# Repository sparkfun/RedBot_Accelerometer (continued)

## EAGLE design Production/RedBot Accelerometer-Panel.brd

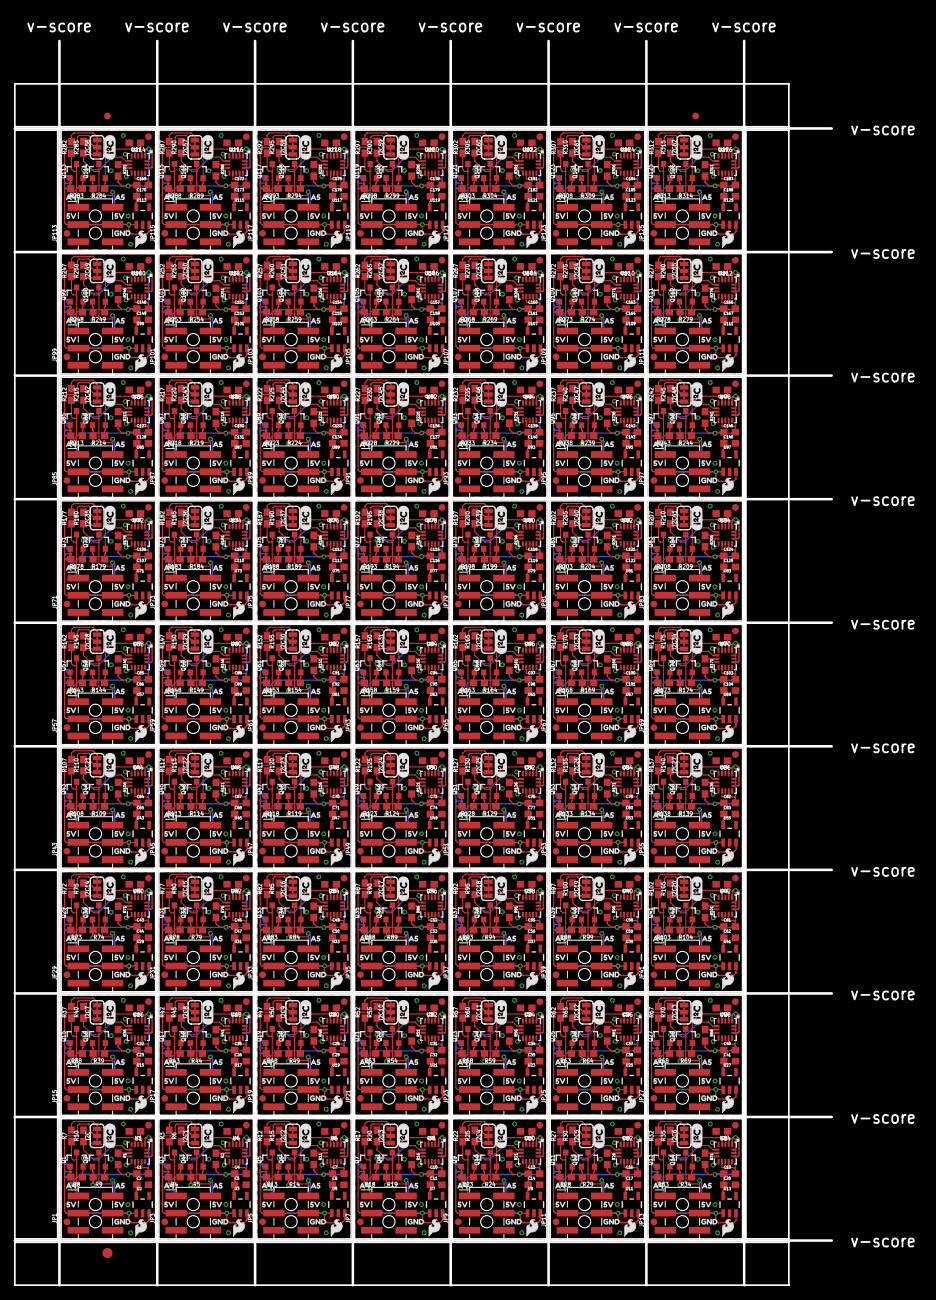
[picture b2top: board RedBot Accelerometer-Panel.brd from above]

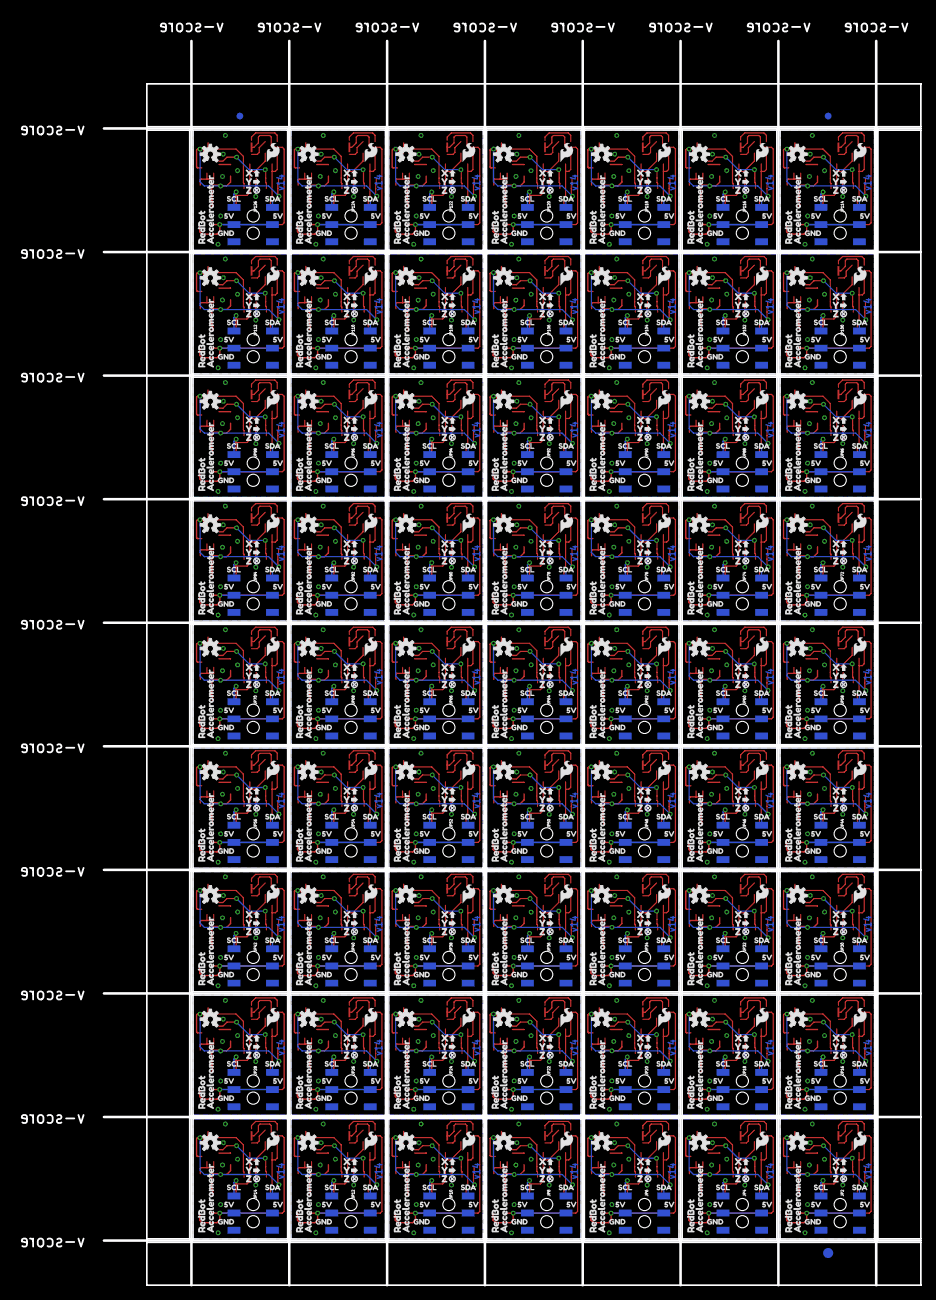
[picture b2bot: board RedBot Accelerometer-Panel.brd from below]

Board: 2 copper layers, 120.9 x 184.2 mm, 2400 parts (948 on the bottom side), 693 nets.

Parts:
C1, C3, C4, C6, C7, C9, C10, C12, C13, C15, C16, C18, C19, C21, C22, C24, C25, C27, C28, C30, C31, C33, C34, C36, C37, C39, C40, C42, C43, C45, C46, C48, C49, C51, C52, C54, C55, C57, C58, C60, C61, C63, C64, C66, C67, C69, C70, C72, C73, C75, C76, C78, C79, C81, C82, C84, C85, C87, C88, C90, C91, C93, C94, C96, C97, C99, C100, C102, C103, C105, C106, C108, C109, C111, C112, C114, C115, C117, C118, C120, C121, C123, C124, C126, C127, C129, C130, C132, C133, C135, C136, C138, C139, C141, C142, C144, C145, C147, C148, C150, C151, C153, C154, C156, C157, C159, C160, C162, C163, C165, C166, C168, C169, C171, C172, C174, C175, C177, C178, C180, C181, C183, C184, C186, C187, C189: 0.1uF; 0603
C2, C5, C8, C11, C14, C17, C20, C23, C26, C29, C32, C35, C38, C41, C44, C47, C50, C53, C56, C59, C62, C65, C68, C71, C74, C77, C80, C83, C86, C89, C92, C95, C98, C101, C104, C107, C110, C113, C116, C119, C122, C125, C128, C131, C134, C137, C140, C143, C146, C149, C152, C155, C158, C161, C164, C167, C170, C173, C176, C179, C182, C185, C188: 4.7uF; 0603
E$1, E$2, E$3, E$4: FIDUCIAL-1X2
E$5, E$6: FIDUCIAL-1.5X3
FID1, FID2, FID3, FID4, FID5, FID6, FID7, FID8, FID9, FID10, FID11, FID12, FID13, FID14, FID15, FID16, FID17, FID18, FID19, FID20, FID21, FID22, FID23, FID24, FID25, FID26, FID27, FID28, FID29, FID30, FID31, FID32, FID33, FID34, FID35, FID36, FID37, FID38, FID39, FID40, FID41, FID42, FID43, FID44, FID45, FID46, FID47, FID48, FID49, FID50, FID51, FID52, FID53, FID54, FID55, FID56, FID57, FID58, FID59, FID60, FID61, FID62, FID63, FID64, FID65, FID66, FID67, FID68, FID69, FID70, FID71, FID72, FID73, FID74, FID75, FID76, FID77, FID78, FID79, FID80, FID81, FID82, FID83, FID84, FID85, FID86, FID87, FID88, FID89, FID90, FID91, FID92, FID93, FID94, FID95, FID96, FID97, FID98, FID99, FID100, FID101, FID102, FID103, FID104, FID105, FID106, FID107, FID108, FID109, FID110, FID111, FID112, FID113, FID114, FID115, FID116, FID117, FID118, FID119, FID120, FID121, FID122, FID123, FID124, FID125, FID126: FIDUCIAL1X2; FIDUCIAL-1X2
I2C, I2C1, I2C2, I2C3, I2C4, I2C5, I2C6, I2C7, I2C8, I2C9, I2C10, I2C11, I2C12, I2C13, I2C14, I2C15, I2C16, I2C17, I2C18, I2C19, I2C20, I2C21, I2C22, I2C23, I2C24, I2C25, I2C26, I2C27, I2C28, I2C29, I2C30, I2C31, I2C32, I2C33, I2C34, I2C35, I2C36, I2C37, I2C38, I2C39, I2C40, I2C41, I2C42, I2C43, I2C44, I2C45, I2C46, I2C47, I2C48, I2C49, I2C50, I2C51, I2C52, I2C53, I2C54, I2C55, I2C56, I2C57, I2C58, I2C59, I2C60, I2C61, I2C62: JUMPER-SMT_3_2-NC_TRACE_SILK; SMT-JUMPER_3_2-NC_TRACE_SILK
JP1, JP3, JP5, JP7, JP9, JP11, JP13, JP15, JP17, JP19, JP21, JP23, JP25, JP27, JP29, JP31, JP33, JP35, JP37, JP39, JP41, JP43, JP45, JP47, JP49, JP51, JP53, JP55, JP57, JP59, JP61, JP63, JP65, JP67, JP69, JP71, JP73, JP75, JP77, JP79, JP81, JP83, JP85, JP87, JP89, JP91, JP93, JP95, JP97, JP99, JP101, JP103, JP105, JP107, JP109, JP111, JP113, JP115, JP117, JP119, JP121, JP123, JP125: 2X3_SMT_POSTS
JP2, JP4, JP6, JP8, JP10, JP12, JP14, JP16, JP18, JP20, JP22, JP24, JP26, JP28, JP30, JP32, JP34, JP36, JP38, JP40, JP42, JP44, JP46, JP48, JP50, JP52, JP54, JP56, JP58, JP60, JP62, JP64, JP66, JP68, JP70, JP72, JP74, JP76, JP78, JP80, JP82, JP84, JP86, JP88, JP90, JP92, JP94, JP96, JP98, JP100, JP102, JP104, JP106, JP108, JP110, JP112, JP114, JP116, JP118, JP120, JP122, JP124, JP126: 2X3_SMD
LOGO1, LOGO2, LOGO7, LOGO10, LOGO13, LOGO16, LOGO19, LOGO22, LOGO25, LOGO28, LOGO31, LOGO34, LOGO37, LOGO40, LOGO43, LOGO46, LOGO49, LOGO52, LOGO55, LOGO58, LOGO61, LOGO64, LOGO67, LOGO70, LOGO73, LOGO76, LOGO79, LOGO82, LOGO85, LOGO88, LOGO91, LOGO94, LOGO97, LOGO100, LOGO103, LOGO106, LOGO109, LOGO112, LOGO115, LOGO118, LOGO121, LOGO124, LOGO127, LOGO130, LOGO133, LOGO136, LOGO139, LOGO142, LOGO145, LOGO148, LOGO151, LOGO154, LOGO157, LOGO160, LOGO163, LOGO166, LOGO169, LOGO172, LOGO175, LOGO178, LOGO181, LOGO184, LOGO187: OSHW-LOGOS; OSHW-LOGO-S
LOGO3, LOGO5, LOGO8, LOGO11, LOGO14, LOGO17, LOGO20, LOGO23, LOGO26, LOGO29, LOGO32, LOGO35, LOGO38, LOGO41, LOGO44, LOGO47, LOGO50, LOGO53, LOGO56, LOGO59, LOGO62, LOGO65, LOGO68, LOGO71, LOGO74, LOGO77, LOGO80, LOGO83, LOGO86, LOGO89, LOGO92, LOGO95, LOGO98, LOGO101, LOGO104, LOGO107, LOGO110, LOGO113, LOGO116, LOGO119, LOGO122, LOGO125, LOGO128, LOGO131, LOGO134, LOGO137, LOGO140, LOGO143, LOGO146, LOGO149, LOGO152, LOGO155, LOGO158, LOGO161, LOGO164, LOGO167, LOGO170, LOGO173, LOGO176, LOGO179, LOGO182, LOGO185, LOGO188: LOGO-SFESK; SFE-LOGO-FLAME
LOGO4, LOGO6, LOGO9, LOGO12, LOGO15, LOGO18, LOGO21, LOGO24, LOGO27, LOGO30, LOGO33, LOGO36, LOGO39, LOGO42, LOGO45, LOGO48, LOGO51, LOGO54, LOGO57, LOGO60, LOGO63, LOGO66, LOGO69, LOGO72, LOGO75, LOGO78, LOGO81, LOGO84, LOGO87, LOGO90, LOGO93, LOGO96, LOGO99, LOGO102, LOGO105, LOGO108, LOGO111, LOGO114, LOGO117, LOGO120, LOGO123, LOGO126, LOGO129, LOGO132, LOGO135, LOGO138, LOGO141, LOGO144, LOGO147, LOGO150, LOGO153, LOGO156, LOGO159, LOGO162, LOGO165, LOGO168, LOGO171, LOGO174, LOGO177, LOGO180, LOGO183, LOGO186, LOGO189: SFE_LOGO_FLAME.1_INCH; SFE_LOGO_FLAME_.1
Q1, Q2, Q3, Q4, Q5, Q6, Q7, Q8, Q9, Q10, Q11, Q12, Q13, Q14, Q15, Q16, Q17, Q18, Q19, Q20, Q21, Q22, Q23, Q24, Q25, Q26, Q27, Q28, Q29, Q30, Q31, Q32, Q33, Q34, Q35, Q36, Q37, Q38, Q39, Q40, Q41, Q42, Q43, Q44, Q45, Q46, Q47, Q48, Q49, Q50, Q51, Q52, Q53, Q54, Q55, Q56, Q57, Q58, Q59, Q60, Q61, Q62, Q63, Q64, Q65, Q66, Q67, Q68, Q69, Q70, Q71, Q72, Q73, Q74, Q75, Q76, Q77, Q78, Q79, Q80, Q81, Q82, Q83, Q84, Q85, Q86, Q87, Q88, Q89, Q90, Q91, Q92, Q93, Q94, Q95, Q96, Q97, Q98, Q99, Q100, Q101, Q102, Q103, Q104, Q105, Q106, Q107, Q108, Q109, Q110, Q111, Q112, Q113, Q114, Q115, Q116, Q117, Q118, Q119, Q120, Q121, Q122, Q123, Q124, Q125, Q126: 220mA/50V/3.5Ω; SOT23-3
R1, R2, R3, R4, R5, R6, R7, R8, R9, R10, R11, R12, R13, R14, R15, R16, R17, R18, R19, R20, R21, R22, R23, R24, R25, R26, R27, R28, R29, R30, R31, R32, R33, R34, R35, R36, R37, R38, R39, R40, R41, R42, R43, R44, R45, R46, R47, R48, R49, R50, R51, R52, R53, R54, R55, R56, R57, R58, R59, R60, R61, R62, R63, R64, R65, R66, R67, R68, R69, R70, R71, R72, R73, R74, R75, R76, R77, R78, R79, R80, R81, R82, R83, R84, R85, R86, R87, R88, R89, R90, R91, R92, R93, R94, R95, R96, R97, R98, R99, R100, R101, R102, R103, R104, R105, R106, R107, R108, R109, R110, R111, R112, R113, R114, R115, R116, R117, R118, R119, R120, R121, R122, R123, R124, R125, R126, R127, R128, R129, R130, R131, R132, R133, R134, R135, R136, R137, R138, R139, R140, R141, R142, R143, R144, R145, R146, R147, R148, R149, R150, R151, R152, R153, R154, R155, R156, R157, R158, R159, R160, R161, R162, R163, R164, R165, R166, R167, R168, R169, R170, R171, R172, R173, R174, R175, R176, R177, R178, R179, R180, R181, R182, R183, R184, R185, R186, R187, R188, R189, R190, R191, R192, R193, R194, R195, R196, R197, R198, R199, R200, R201, R202, R203, R204, R205, R206, R207, R208, R209, R210, R211, R212, R213, R214, R215, R216, R217, R218, R219, R220, R221, R222, R223, R224, R225, R226, R227, R228, R229, R230, R231, R232, R233, R234, R235, R236, R237, R238, R239, R240, R241, R242, R243, R244, R245, R246, R247, R248, R249, R250, R251, R252, R253, R254, R255, R256, R257, R258, R259, R260, R261, R262, R263, R264, R265, R266, R267, R268, R269, R270, R271, R272, R273, R274, R275, R276, R277, R278, R279, R280, R281, R282, R283, R284, R285, R286, R287, R288, R289, R290, R291, R292, R293, R294, R295, R296, R297, R298, R299, R300, R301, R302, R303, R304, R305, R306, R307, R308, R309, R310, R311, R312, R313, R314, R315: 10k; 0603
U1, U4, U6, U8, U10, U12, U14, U16, U18, U20, U22, U24, U26, U28, U30, U32, U34, U36, U38, U40, U42, U44, U46, U48, U50, U52, U54, U56, U58, U60, U62, U64, U66, U68, U70, U72, U74, U76, U78, U80, U82, U84, U86, U88, U90, U92, U94, U96, U98, U100, U102, U104, U106, U108, U110, U112, U114, U116, U118, U120, U122, U124, U126: MMA8452Q; QFN-16
U2, U3, U5, U7, U9, U11, U13, U15, U17, U19, U21, U23, U25, U27, U29, U31, U33, U35, U37, U39, U41, U43, U45, U47, U49, U51, U53, U55, U57, U59, U61, U63, U65, U67, U69, U71, U73, U75, U77, U79, U81, U83, U85, U87, U89, U91, U93, U95, U97, U99, U101, U103, U105, U107, U109, U111, U113, U115, U117, U119, U121, U123, U125: MIC5205-3.3V; SOT23-5
U$1, U$18, U$37, U$55, U$73, U$91, U$109, U$127, U$145, U$163, U$181, U$199, U$217, U$235, U$253, U$271, U$289, U$307, U$325, U$343, U$361, U$379, U$397, U$415, U$433, U$451, U$469, U$487, U$505, U$523, U$541, U$559, U$577, U$595, U$613, U$631, U$649, U$667, U$685, U$703, U$721, U$739, U$757, U$775, U$793, U$811, U$829, U$847, U$865, U$883, U$901, U$919, U$937, U$955, U$973, U$991, U$1009, U$1027, U$1045, U$1063, U$1081, U$1099, U$1117: X0
U$2, U$20, U$38, U$56, U$74, U$92, U$110, U$128, U$146, U$164, U$182, U$200, U$218, U$236, U$254, U$272, U$290, U$308, U$326, U$344, U$362, U$380, U$398, U$416, U$434, U$452, U$470, U$488, U$506, U$524, U$542, U$560, U$578, U$596, U$614, U$632, U$650, U$668, U$686, U$704, U$722, U$740, U$758, U$776, U$794, U$812, U$830, U$848, U$866, U$884, U$902, U$920, U$938, U$956, U$974, U$992, U$1010, U$1028, U$1046, U$1064, U$1082, U$1100, U$1118: A42
U$3, U$21, U$39, U$57, U$75, U$93, U$111, U$129, U$147, U$165, U$183, U$201, U$219, U$237, U$255, U$273, U$291, U$309, U$327, U$345, U$363, U$381, U$399, U$417, U$435, U$453, U$471, U$489, U$507, U$525, U$543, U$561, U$579, U$597, U$615, U$633, U$651, U$669, U$687, U$705, U$723, U$741, U$759, U$777, U$795, U$813, U$831, U$849, U$867, U$885, U$903, U$921, U$939, U$957, U$975, U$993, U$1011, U$1029, U$1047, U$1065, U$1083, U$1101, U$1119: A53
U$4, U$5, U$8, U$11, U$22, U$23, U$26, U$29, U$40, U$41, U$44, U$47, U$58, U$59, U$62, U$65, U$76, U$77, U$80, U$83, U$94, U$95, U$98, U$101, U$112, U$113, U$116, U$119, U$130, U$131, U$134, U$137, U$148, U$149, U$152, U$155, U$166, U$167, U$170, U$173, U$184, U$185, U$188, U$191, U$202, U$203, U$206, U$209, U$220, U$221, U$224, U$227, U$238, U$239, U$242, U$245, U$256, U$257, U$260, U$263, U$274, U$275, U$278, U$281, U$292, U$293, U$296, U$299, U$310, U$311, U$314, U$317, U$328, U$329, U$332, U$335, U$346, U$347, U$350, U$353, U$364, U$365, U$368, U$371, U$382, U$383, U$386, U$389, U$400, U$401, U$404, U$407, U$418, U$419, U$422, U$425, U$436, U$437, U$440, U$443, U$454, U$455, U$458, U$461, U$472, U$473, U$476, U$479, U$490, U$491, U$494, U$497, U$508, U$509, U$512, U$515, U$526, U$527, U$530, U$533, U$544, U$545, U$548, U$551, U$562, U$563, U$566, U$569, U$580, U$581, U$584, U$587, U$598, U$599, U$602, U$605, U$616, U$617, U$620, U$623, U$634, U$635, U$638, U$641, U$652, U$653, U$656, U$659, U$670, U$671, U$674, U$677, U$688, U$689, U$692, U$695, U$706, U$707, U$710, U$713, U$724, U$725, U$728, U$731, U$742, U$743, U$746, U$749, U$760, U$761, U$764, U$767, U$778, U$779, U$782, U$785, U$796, U$797, U$800, U$803, U$814, U$815, U$818, U$821, U$832, U$833, U$836, U$839, U$850, U$851, U$854, U$857, U$868, U$869, U$872, U$875, U$886, U$887, U$890, U$893, U$904, U$905, U$908, U$911, U$922, U$923, U$926, U$929, U$940, U$941, U$944, U$947, U$958, U$959, U$962, U$965, U$976, U$977, U$980, U$983, U$994, U$995, U$998, U$1001, U$1012, U$1013, U$1016, U$1019, U$1030, U$1031, U$1034, U$1037, U$1048, U$1049, U$1052, U$1055, U$1066, U$1067, U$1070, U$1073, U$1084, U$1085, U$1088, U$1091, U$1102, U$1103, U$1106, U$1109, U$1120, U$1121, U$1124, U$1127: _5V1
U$6, U$7, U$24, U$25, U$42, U$43, U$60, U$61, U$78, U$79, U$96, U$97, U$114, U$115, U$132, U$133, U$150, U$151, U$168, U$169, U$186, U$187, U$204, U$205, U$222, U$223, U$240, U$241, U$258, U$259, U$276, U$277, U$294, U$295, U$312, U$313, U$330, U$331, U$348, U$349, U$366, U$367, U$384, U$385, U$402, U$403, U$420, U$421, U$438, U$439, U$456, U$457, U$474, U$475, U$492, U$493, U$510, U$511, U$528, U$529, U$546, U$547, U$564, U$565, U$582, U$583, U$600, U$601, U$618, U$619, U$636, U$637, U$654, U$655, U$672, U$673, U$690, U$691, U$708, U$709, U$726, U$727, U$744, U$745, U$762, U$763, U$780, U$781, U$798, U$799, U$816, U$817, U$834, U$835, U$852, U$853, U$870, U$871, U$888, U$889, U$906, U$907, U$924, U$925, U$942, U$943, U$960, U$961, U$978, U$979, U$996, U$997, U$1014, U$1015, U$1032, U$1033, U$1050, U$1051, U$1068, U$1069, U$1086, U$1087, U$1104, U$1105, U$1122, U$1123: GND0
U$9, U$27, U$45, U$63, U$81, U$99, U$117, U$135, U$153, U$171, U$189, U$207, U$225, U$243, U$261, U$279, U$297, U$315, U$333, U$351, U$369, U$387, U$405, U$423, U$441, U$459, U$477, U$495, U$513, U$531, U$549, U$567, U$585, U$603, U$621, U$639, U$657, U$675, U$693, U$711, U$729, U$747, U$765, U$783, U$801, U$819, U$837, U$855, U$873, U$891, U$909, U$927, U$945, U$963, U$981, U$999, U$1017, U$1035, U$1053, U$1071, U$1089, U$1107, U$1125: SDA6
U$10, U$28, U$46, U$64, U$82, U$100, U$118, U$136, U$154, U$172, U$190, U$208, U$226, U$244, U$262, U$280, U$298, U$316, U$334, U$352, U$370, U$388, U$406, U$424, U$442, U$460, U$478, U$496, U$514, U$532, U$550, U$568, U$586, U$604, U$622, U$640, U$658, U$676, U$694, U$712, U$730, U$748, U$766, U$784, U$802, U$820, U$838, U$856, U$874, U$892, U$910, U$928, U$946, U$964, U$982, U$1000, U$1018, U$1036, U$1054, U$1072, U$1090, U$1108, U$1126: _SCL7
U$12, U$30, U$48, U$66, U$84, U$102, U$120, U$138, U$156, U$174, U$192, U$210, U$228, U$246, U$264, U$282, U$300, U$318, U$336, U$354, U$372, U$390, U$408, U$426, U$444, U$462, U$480, U$498, U$516, U$534, U$552, U$570, U$588, U$606, U$624, U$642, U$660, U$678, U$696, U$714, U$732, U$750, U$768, U$786, U$804, U$822, U$840, U$858, U$876, U$894, U$912, U$930, U$948, U$966, U$984, U$1002, U$1020, U$1038, U$1056, U$1074, U$1092, U$1110, U$1128: ##3
U$13, U$31, U$49, U$67, U$85, U$103, U$121, U$139, U$157, U$175, U$193, U$211, U$229, U$247, U$265, U$283, U$301, U$319, U$337, U$355, U$373, U$391, U$409, U$427, U$445, U$463, U$481, U$499, U$517, U$535, U$553, U$571, U$589, U$607, U$625, U$643, U$661, U$679, U$697, U$715, U$733, U$751, U$769, U$787, U$805, U$823, U$841, U$859, U$877, U$895, U$913, U$931, U$949, U$967, U$985, U$1003, U$1021, U$1039, U$1057, U$1075, U$1093, U$1111, U$1129: ##4
U$14, U$32, U$50, U$68, U$86, U$104, U$122, U$140, U$158, U$176, U$194, U$212, U$230, U$248, U$266, U$284, U$302, U$320, U$338, U$356, U$374, U$392, U$410, U$428, U$446, U$464, U$482, U$500, U$518, U$536, U$554, U$572, U$590, U$608, U$626, U$644, U$662, U$680, U$698, U$716, U$734, U$752, U$770, U$788, U$806, U$824, U$842, U$860, U$878, U$896, U$914, U$932, U$950, U$968, U$986, U$1004, U$1022, U$1040, U$1058, U$1076, U$1094, U$1112, U$1130: Y1
U$15, U$33, U$51, U$69, U$87, U$105, U$123, U$141, U$159, U$177, U$195, U$213, U$231, U$249, U$267, U$285, U$303, U$321, U$339, U$357, U$375, U$393, U$411, U$429, U$447, U$465, U$483, U$501, U$519, U$537, U$555, U$573, U$591, U$609, U$627, U$645, U$663, U$681, U$699, U$717, U$735, U$753, U$771, U$789, U$807, U$825, U$843, U$861, U$879, U$897, U$915, U$933, U$951, U$969, U$987, U$1005, U$1023, U$1041, U$1059, U$1077, U$1095, U$1113, U$1131: Z2
U$16, U$34, U$52, U$70, U$88, U$106, U$124, U$142, U$160, U$178, U$196, U$214, U$232, U$250, U$268, U$286, U$304, U$322, U$340, U$358, U$376, U$394, U$412, U$430, U$448, U$466, U$484, U$502, U$520, U$538, U$556, U$574, U$592, U$610, U$628, U$646, U$664, U$682, U$700, U$718, U$736, U$754, U$772, U$790, U$808, U$826, U$844, U$862, U$880, U$898, U$916, U$934, U$952, U$970, U$988, U$1006, U$1024, U$1042, U$1060, U$1078, U$1096, U$1114, U$1132: REDBOT4
U$17, U$35, U$53, U$71, U$89, U$107, U$125, U$143, U$161, U$179, U$197, U$215, U$233, U$251, U$269, U$287, U$305, U$323, U$341, U$359, U$377, U$395, U$413, U$431, U$449, U$467, U$485, U$503, U$521, U$539, U$557, U$575, U$593, U$611, U$629, U$647, U$665, U$683, U$701, U$719, U$737, U$755, U$773, U$791, U$809, U$827, U$845, U$863, U$881, U$899, U$917, U$935, U$953, U$971, U$989, U$1007, U$1025, U$1043, U$1061, U$1079, U$1097, U$1115, U$1133: ACCELEROMETER5
U$19, U$36, U$54, U$72, U$90, U$108, U$126, U$144, U$162, U$180, U$198, U$216, U$234, U$252, U$270, U$288, U$306, U$324, U$342, U$360, U$378, U$396, U$414, U$432, U$450, U$468, U$486, U$504, U$522, U$540, U$558, U$576, U$594, U$612, U$630, U$648, U$666, U$684, U$702, U$720, U$738, U$756, U$774, U$792, U$810, U$828, U$846, U$864, U$882, U$900, U$918, U$936, U$954, U$972, U$990, U$1008, U$1026, U$1044, U$1062, U$1080, U$1098, U$1116, U$1134: I2C

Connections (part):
3.3V: C1.1, C2.1, Q1.1, Q2.1, R1.2, R8.2, R9.2, U1.1, U1.14, U2.5
3.3V1: C4.1, C5.1, Q3.1, Q4.1, R2.2, R4.2, R5.2, U3.5, U4.1, U4.14
3.3V2: C7.1, C8.1, Q5.1, Q6.1, R11.2, R13.2, R14.2, U5.5, U6.1, U6.14
3.3V3: C10.1, C11.1, Q7.1, Q8.1, R16.2, R18.2, R19.2, U7.5, U8.1, U8.14
3.3V4: C13.1, C14.1, Q9.1, Q10.1, R21.2, R23.2, R24.2, U9.5, U10.1, U10.14
3.3V5: C16.1, C17.1, Q11.1, Q12.1, R26.2, R28.2, R29.2, U11.5, U12.1, U12.14
3.3V6: C19.1, C20.1, Q13.1, Q14.1, R31.2, R33.2, R34.2, U13.5, U14.1, U14.14
3.3V7: C22.1, C23.1, Q15.1, Q16.1, R36.2, R38.2, R39.2, U15.5, U16.1, U16.14
3.3V8: C25.1, C26.1, Q17.1, Q18.1, R41.2, R43.2, R44.2, U17.5, U18.1, U18.14
3.3V9: C28.1, C29.1, Q19.1, Q20.1, R46.2, R48.2, R49.2, U19.5, U20.1, U20.14
3.3V10: C31.1, C32.1, Q21.1, Q22.1, R51.2, R53.2, R54.2, U21.5, U22.1, U22.14
3.3V11: C34.1, C35.1, Q23.1, Q24.1, R56.2, R58.2, R59.2, U23.5, U24.1, U24.14
3.3V12: C37.1, C38.1, Q25.1, Q26.1, R61.2, R63.2, R64.2, U25.5, U26.1, U26.14
3.3V13: C40.1, C41.1, Q27.1, Q28.1, R66.2, R68.2, R69.2, U27.5, U28.1, U28.14
3.3V14: C43.1, C44.1, Q29.1, Q30.1, R71.2, R73.2, R74.2, U29.5, U30.1, U30.14
3.3V15: C46.1, C47.1, Q31.1, Q32.1, R76.2, R78.2, R79.2, U31.5, U32.1, U32.14
3.3V16: C49.1, C50.1, Q33.1, Q34.1, R81.2, R83.2, R84.2, U33.5, U34.1, U34.14
3.3V17: C52.1, C53.1, Q35.1, Q36.1, R86.2, R88.2, R89.2, U35.5, U36.1, U36.14
3.3V18: C55.1, C56.1, Q37.1, Q38.1, R91.2, R93.2, R94.2, U37.5, U38.1, U38.14
3.3V19: C58.1, C59.1, Q39.1, Q40.1, R96.2, R98.2, R99.2, U39.5, U40.1, U40.14
3.3V20: C61.1, C62.1, Q41.1, Q42.1, R101.2, R103.2, R104.2, U41.5, U42.1, U42.14
3.3V21: C64.1, C65.1, Q43.1, Q44.1, R106.2, R108.2, R109.2, U43.5, U44.1, U44.14
3.3V22: C67.1, C68.1, Q45.1, Q46.1, R111.2, R113.2, R114.2, U45.5, U46.1, U46.14
3.3V23: C70.1, C71.1, Q47.1, Q48.1, R116.2, R118.2, R119.2, U47.5, U48.1, U48.14
3.3V24: C73.1, C74.1, Q49.1, Q50.1, R121.2, R123.2, R124.2, U49.5, U50.1, U50.14
3.3V25: C76.1, C77.1, Q51.1, Q52.1, R126.2, R128.2, R129.2, U51.5, U52.1, U52.14
3.3V26: C79.1, C80.1, Q53.1, Q54.1, R131.2, R133.2, R134.2, U53.5, U54.1, U54.14
3.3V27: C82.1, C83.1, Q55.1, Q56.1, R136.2, R138.2, R139.2, U55.5, U56.1, U56.14
3.3V28: C85.1, C86.1, Q57.1, Q58.1, R141.2, R143.2, R144.2, U57.5, U58.1, U58.14
3.3V29: C88.1, C89.1, Q59.1, Q60.1, R146.2, R148.2, R149.2, U59.5, U60.1, U60.14
3.3V30: C91.1, C92.1, Q61.1, Q62.1, R151.2, R153.2, R154.2, U61.5, U62.1, U62.14
3.3V31: C94.1, C95.1, Q63.1, Q64.1, R156.2, R158.2, R159.2, U63.5, U64.1, U64.14
3.3V32: C97.1, C98.1, Q65.1, Q66.1, R161.2, R163.2, R164.2, U65.5, U66.1, U66.14
3.3V33: C100.1, C101.1, Q67.1, Q68.1, R166.2, R168.2, R169.2, U67.5, U68.1, U68.14
3.3V34: C103.1, C104.1, Q69.1, Q70.1, R171.2, R173.2, R174.2, U69.5, U70.1, U70.14
3.3V35: C106.1, C107.1, Q71.1, Q72.1, R176.2, R178.2, R179.2, U71.5, U72.1, U72.14
3.3V36: C109.1, C110.1, Q73.1, Q74.1, R181.2, R183.2, R184.2, U73.5, U74.1, U74.14
3.3V37: C112.1, C113.1, Q75.1, Q76.1, R186.2, R188.2, R189.2, U75.5, U76.1, U76.14
3.3V38: C115.1, C116.1, Q77.1, Q78.1, R191.2, R193.2, R194.2, U77.5, U78.1, U78.14
3.3V39: C118.1, C119.1, Q79.1, Q80.1, R196.2, R198.2, R199.2, U79.5, U80.1, U80.14
3.3V40: C121.1, C122.1, Q81.1, Q82.1, R201.2, R203.2, R204.2, U81.5, U82.1, U82.14
3.3V41: C124.1, C125.1, Q83.1, Q84.1, R206.2, R208.2, R209.2, U83.5, U84.1, U84.14
3.3V42: C127.1, C128.1, Q85.1, Q86.1, R211.2, R213.2, R214.2, U85.5, U86.1, U86.14
3.3V43: C130.1, C131.1, Q87.1, Q88.1, R216.2, R218.2, R219.2, U87.5, U88.1, U88.14
3.3V44: C133.1, C134.1, Q89.1, Q90.1, R221.2, R223.2, R224.2, U89.5, U90.1, U90.14
3.3V45: C136.1, C137.1, Q91.1, Q92.1, R226.2, R228.2, R229.2, U91.5, U92.1, U92.14
3.3V46: C139.1, C140.1, Q93.1, Q94.1, R231.2, R233.2, R234.2, U93.5, U94.1, U94.14
3.3V47: C142.1, C143.1, Q95.1, Q96.1, R236.2, R238.2, R239.2, U95.5, U96.1, U96.14
3.3V48: C145.1, C146.1, Q97.1, Q98.1, R241.2, R243.2, R244.2, U97.5, U98.1, U98.14
3.3V49: C148.1, C149.1, Q99.1, Q100.1, R246.2, R248.2, R249.2, U99.5, U100.1, U100.14
3.3V50: C151.1, C152.1, Q101.1, Q102.1, R251.2, R253.2, R254.2, U101.5, U102.1, U102.14
3.3V51: C154.1, C155.1, Q103.1, Q104.1, R256.2, R258.2, R259.2, U103.5, U104.1, U104.14
3.3V52: C157.1, C158.1, Q105.1, Q106.1, R261.2, R263.2, R264.2, U105.5, U106.1, U106.14
3.3V53: C160.1, C161.1, Q107.1, Q108.1, R266.2, R268.2, R269.2, U107.5, U108.1, U108.14
3.3V54: C163.1, C164.1, Q109.1, Q110.1, R271.2, R273.2, R274.2, U109.5, U110.1, U110.14
3.3V55: C166.1, C167.1, Q111.1, Q112.1, R276.2, R278.2, R279.2, U111.5, U112.1, U112.14
3.3V56: C169.1, C170.1, Q113.1, Q114.1, R281.2, R283.2, R284.2, U113.5, U114.1, U114.14
3.3V57: C172.1, C173.1, Q115.1, Q116.1, R286.2, R288.2, R289.2, U115.5, U116.1, U116.14
3.3V58: C175.1, C176.1, Q117.1, Q118.1, R291.2, R293.2, R294.2, U117.5, U118.1, U118.14
3.3V59: C178.1, C179.1, Q119.1, Q120.1, R296.2, R298.2, R299.2, U119.5, U120.1, U120.14
3.3V60: C181.1, C182.1, Q121.1, Q122.1, R301.2, R303.2, R304.2, U121.5, U122.1, U122.14
3.3V61: C184.1, C185.1, Q123.1, Q124.1, R306.2, R308.2, R309.2, U123.5, U124.1, U124.14
3.3V62: C187.1, C188.1, Q125.1, Q126.1, R311.2, R313.2, R314.2, U125.5, U126.1, U126.14
5V: I2C.2, JP1.3, JP1.4, JP2.3, JP2.4, U2.1, U2.3
5V1: I2C1.2, JP3.3, JP3.4, JP4.3, JP4.4, U3.1, U3.3
5V2: I2C2.2, JP5.3, JP5.4, JP6.3, JP6.4, U5.1, U5.3
5V3: I2C3.2, JP7.3, JP7.4, JP8.3, JP8.4, U7.1, U7.3
5V4: I2C4.2, JP9.3, JP9.4, JP10.3, JP10.4, U9.1, U9.3
5V5: I2C5.2, JP11.3, JP11.4, JP12.3, JP12.4, U11.1, U11.3
5V6: I2C6.2, JP13.3, JP13.4, JP14.3, JP14.4, U13.1, U13.3
5V7: I2C7.2, JP15.3, JP15.4, JP16.3, JP16.4, U15.1, U15.3
5V8: I2C8.2, JP17.3, JP17.4, JP18.3, JP18.4, U17.1, U17.3
5V9: I2C9.2, JP19.3, JP19.4, JP20.3, JP20.4, U19.1, U19.3
5V10: I2C10.2, JP21.3, JP21.4, JP22.3, JP22.4, U21.1, U21.3
5V11: I2C11.2, JP23.3, JP23.4, JP24.3, JP24.4, U23.1, U23.3
5V12: I2C12.2, JP25.3, JP25.4, JP26.3, JP26.4, U25.1, U25.3
5V13: I2C13.2, JP27.3, JP27.4, JP28.3, JP28.4, U27.1, U27.3
5V14: I2C14.2, JP29.3, JP29.4, JP30.3, JP30.4, U29.1, U29.3
5V15: I2C15.2, JP31.3, JP31.4, JP32.3, JP32.4, U31.1, U31.3
5V16: I2C16.2, JP33.3, JP33.4, JP34.3, JP34.4, U33.1, U33.3
5V17: I2C17.2, JP35.3, JP35.4, JP36.3, JP36.4, U35.1, U35.3
5V18: I2C18.2, JP37.3, JP37.4, JP38.3, JP38.4, U37.1, U37.3
5V19: I2C19.2, JP39.3, JP39.4, JP40.3, JP40.4, U39.1, U39.3
5V20: I2C20.2, JP41.3, JP41.4, JP42.3, JP42.4, U41.1, U41.3
5V21: I2C21.2, JP43.3, JP43.4, JP44.3, JP44.4, U43.1, U43.3
5V22: I2C22.2, JP45.3, JP45.4, JP46.3, JP46.4, U45.1, U45.3
5V23: I2C23.2, JP47.3, JP47.4, JP48.3, JP48.4, U47.1, U47.3
5V24: I2C24.2, JP49.3, JP49.4, JP50.3, JP50.4, U49.1, U49.3
5V25: I2C25.2, JP51.3, JP51.4, JP52.3, JP52.4, U51.1, U51.3
5V26: I2C26.2, JP53.3, JP53.4, JP54.3, JP54.4, U53.1, U53.3
5V27: I2C27.2, JP55.3, JP55.4, JP56.3, JP56.4, U55.1, U55.3
5V28: I2C28.2, JP57.3, JP57.4, JP58.3, JP58.4, U57.1, U57.3
5V29: I2C29.2, JP59.3, JP59.4, JP60.3, JP60.4, U59.1, U59.3
5V30: I2C30.2, JP61.3, JP61.4, JP62.3, JP62.4, U61.1, U61.3
5V31: I2C31.2, JP63.3, JP63.4, JP64.3, JP64.4, U63.1, U63.3
5V32: I2C32.2, JP65.3, JP65.4, JP66.3, JP66.4, U65.1, U65.3
5V33: I2C33.2, JP67.3, JP67.4, JP68.3, JP68.4, U67.1, U67.3
5V34: I2C34.2, JP69.3, JP69.4, JP70.3, JP70.4, U69.1, U69.3
5V35: I2C35.2, JP71.3, JP71.4, JP72.3, JP72.4, U71.1, U71.3
5V36: I2C36.2, JP73.3, JP73.4, JP74.3, JP74.4, U73.1, U73.3
5V37: I2C37.2, JP75.3, JP75.4, JP76.3, JP76.4, U75.1, U75.3
5V38: I2C38.2, JP77.3, JP77.4, JP78.3, JP78.4, U77.1, U77.3
5V39: I2C39.2, JP79.3, JP79.4, JP80.3, JP80.4, U79.1, U79.3
5V40: I2C40.2, JP81.3, JP81.4, JP82.3, JP82.4, U81.1, U81.3
5V41: I2C41.2, JP83.3, JP83.4, JP84.3, JP84.4, U83.1, U83.3
5V42: I2C42.2, JP85.3, JP85.4, JP86.3, JP86.4, U85.1, U85.3
5V43: I2C43.2, JP87.3, JP87.4, JP88.3, JP88.4, U87.1, U87.3
5V44: I2C44.2, JP89.3, JP89.4, JP90.3, JP90.4, U89.1, U89.3
5V45: I2C45.2, JP91.3, JP91.4, JP92.3, JP92.4, U91.1, U91.3
5V46: I2C46.2, JP93.3, JP93.4, JP94.3, JP94.4, U93.1, U93.3
5V47: I2C47.2, JP95.3, JP95.4, JP96.3, JP96.4, U95.1, U95.3
5V48: I2C48.2, JP97.3, JP97.4, JP98.3, JP98.4, U97.1, U97.3
5V49: I2C49.2, JP99.3, JP99.4, JP100.3, JP100.4, U99.1, U99.3
5V50: I2C50.2, JP101.3, JP101.4, JP102.3, JP102.4, U101.1, U101.3
5V51: I2C51.2, JP103.3, JP103.4, JP104.3, JP104.4, U103.1, U103.3
5V52: I2C52.2, JP105.3, JP105.4, JP106.3, JP106.4, U105.1, U105.3
5V53: I2C53.2, JP107.3, JP107.4, JP108.3, JP108.4, U107.1, U107.3
5V54: I2C54.2, JP109.3, JP109.4, JP110.3, JP110.4, U109.1, U109.3
5V55: I2C55.2, JP111.3, JP111.4, JP112.3, JP112.4, U111.1, U111.3
5V56: I2C56.2, JP113.3, JP113.4, JP114.3, JP114.4, U113.1, U113.3
5V57: I2C57.2, JP115.3, JP115.4, JP116.3, JP116.4, U115.1, U115.3
5V58: I2C58.2, JP117.3, JP117.4, JP118.3, JP118.4, U117.1, U117.3
5V59: I2C59.2, JP119.3, JP119.4, JP120.3, JP120.4, U119.1, U119.3
5V60: I2C60.2, JP121.3, JP121.4, JP122.3, JP122.4, U121.1, U121.3
5V61: I2C61.2, JP123.3, JP123.4, JP124.3, JP124.4, U123.1, U123.3
5V62: I2C62.2, JP125.3, JP125.4, JP126.3, JP126.4, U125.1, U125.3
ADDR: R1.1, U1.7
ADDR1: R2.1, U4.7
ADDR2: R11.1, U6.7
ADDR3: R16.1, U8.7
ADDR4: R21.1, U10.7
ADDR5: R26.1, U12.7
ADDR6: R31.1, U14.7
ADDR7: R36.1, U16.7
ADDR8: R41.1, U18.7
ADDR9: R46.1, U20.7
ADDR10: R51.1, U22.7
ADDR11: R56.1, U24.7
ADDR12: R61.1, U26.7
ADDR13: R66.1, U28.7
ADDR14: R71.1, U30.7
ADDR15: R76.1, U32.7
ADDR16: R81.1, U34.7
ADDR17: R86.1, U36.7
ADDR18: R91.1, U38.7
ADDR19: R96.1, U40.7
ADDR20: R101.1, U42.7
ADDR21: R106.1, U44.7
ADDR22: R111.1, U46.7
ADDR23: R116.1, U48.7
ADDR24: R121.1, U50.7
ADDR25: R126.1, U52.7
ADDR26: R131.1, U54.7
ADDR27: R136.1, U56.7
ADDR28: R141.1, U58.7
ADDR29: R146.1, U60.7
ADDR30: R151.1, U62.7
ADDR31: R156.1, U64.7
ADDR32: R161.1, U66.7
ADDR33: R166.1, U68.7
ADDR34: R171.1, U70.7
ADDR35: R176.1, U72.7
ADDR36: R181.1, U74.7
ADDR37: R186.1, U76.7
ADDR38: R191.1, U78.7
ADDR39: R196.1, U80.7
ADDR40: R201.1, U82.7
ADDR41: R206.1, U84.7
ADDR42: R211.1, U86.7
ADDR43: R216.1, U88.7
ADDR44: R221.1, U90.7
ADDR45: R226.1, U92.7
ADDR46: R231.1, U94.7
ADDR47: R236.1, U96.7
ADDR48: R241.1, U98.7
ADDR49: R246.1, U100.7
ADDR50: R251.1, U102.7
ADDR51: R256.1, U104.7
ADDR52: R261.1, U106.7
ADDR53: R266.1, U108.7
ADDR54: R271.1, U110.7
ADDR55: R276.1, U112.7
ADDR56: R281.1, U114.7
ADDR57: R286.1, U116.7
ADDR58: R291.1, U118.7
ADDR59: R296.1, U120.7
ADDR60: R301.1, U122.7
ADDR61: R306.1, U124.7
ADDR62: R311.1, U126.7
GND: C1.2, C2.2, C3.2, JP1.5, JP1.6, JP2.5, JP2.6, U1.5, U1.10, U1.12, U2.2
GND1: C4.2, C5.2, C6.2, JP3.5, JP3.6, JP4.5, JP4.6, U3.2, U4.5, U4.10, U4.12
GND2: C7.2, C8.2, C9.2, JP5.5, JP5.6, JP6.5, JP6.6, U5.2, U6.5, U6.10, U6.12
GND3: C10.2, C11.2, C12.2, JP7.5, JP7.6, JP8.5, JP8.6, U7.2, U8.5, U8.10, U8.12
GND4: C13.2, C14.2, C15.2, JP9.5, JP9.6, JP10.5, JP10.6, U9.2, U10.5, U10.10, U10.12
GND5: C16.2, C17.2, C18.2, JP11.5, JP11.6, JP12.5, JP12.6, U11.2, U12.5, U12.10, U12.12
GND6: C19.2, C20.2, C21.2, JP13.5, JP13.6, JP14.5, JP14.6, U13.2, U14.5, U14.10, U14.12
GND7: C22.2, C23.2, C24.2, JP15.5, JP15.6, JP16.5, JP16.6, U15.2, U16.5, U16.10, U16.12
GND8: C25.2, C26.2, C27.2, JP17.5, JP17.6, JP18.5, JP18.6, U17.2, U18.5, U18.10, U18.12
GND9: C28.2, C29.2, C30.2, JP19.5, JP19.6, JP20.5, JP20.6, U19.2, U20.5, U20.10, U20.12
GND10: C31.2, C32.2, C33.2, JP21.5, JP21.6, JP22.5, JP22.6, U21.2, U22.5, U22.10, U22.12
GND11: C34.2, C35.2, C36.2, JP23.5, JP23.6, JP24.5, JP24.6, U23.2, U24.5, U24.10, U24.12
GND12: C37.2, C38.2, C39.2, JP25.5, JP25.6, JP26.5, JP26.6, U25.2, U26.5, U26.10, U26.12
GND13: C40.2, C41.2, C42.2, JP27.5, JP27.6, JP28.5, JP28.6, U27.2, U28.5, U28.10, U28.12
GND14: C43.2, C44.2, C45.2, JP29.5, JP29.6, JP30.5, JP30.6, U29.2, U30.5, U30.10, U30.12
GND15: C46.2, C47.2, C48.2, JP31.5, JP31.6, JP32.5, JP32.6, U31.2, U32.5, U32.10, U32.12
GND16: C49.2, C50.2, C51.2, JP33.5, JP33.6, JP34.5, JP34.6, U33.2, U34.5, U34.10, U34.12
GND17: C52.2, C53.2, C54.2, JP35.5, JP35.6, JP36.5, JP36.6, U35.2, U36.5, U36.10, U36.12
GND18: C55.2, C56.2, C57.2, JP37.5, JP37.6, JP38.5, JP38.6, U37.2, U38.5, U38.10, U38.12
GND19: C58.2, C59.2, C60.2, JP39.5, JP39.6, JP40.5, JP40.6, U39.2, U40.5, U40.10, U40.12
GND20: C61.2, C62.2, C63.2, JP41.5, JP41.6, JP42.5, JP42.6, U41.2, U42.5, U42.10, U42.12
GND21: C64.2, C65.2, C66.2, JP43.5, JP43.6, JP44.5, JP44.6, U43.2, U44.5, U44.10, U44.12
GND22: C67.2, C68.2, C69.2, JP45.5, JP45.6, JP46.5, JP46.6, U45.2, U46.5, U46.10, U46.12
GND23: C70.2, C71.2, C72.2, JP47.5, JP47.6, JP48.5, JP48.6, U47.2, U48.5, U48.10, U48.12
GND24: C73.2, C74.2, C75.2, JP49.5, JP49.6, JP50.5, JP50.6, U49.2, U50.5, U50.10, U50.12
GND25: C76.2, C77.2, C78.2, JP51.5, JP51.6, JP52.5, JP52.6, U51.2, U52.5, U52.10, U52.12
GND26: C79.2, C80.2, C81.2, JP53.5, JP53.6, JP54.5, JP54.6, U53.2, U54.5, U54.10, U54.12
GND27: C82.2, C83.2, C84.2, JP55.5, JP55.6, JP56.5, JP56.6, U55.2, U56.5, U56.10, U56.12
GND28: C85.2, C86.2, C87.2, JP57.5, JP57.6, JP58.5, JP58.6, U57.2, U58.5, U58.10, U58.12
GND29: C88.2, C89.2, C90.2, JP59.5, JP59.6, JP60.5, JP60.6, U59.2, U60.5, U60.10, U60.12
GND30: C91.2, C92.2, C93.2, JP61.5, JP61.6, JP62.5, JP62.6, U61.2, U62.5, U62.10, U62.12
GND31: C94.2, C95.2, C96.2, JP63.5, JP63.6, JP64.5, JP64.6, U63.2, U64.5, U64.10, U64.12
GND32: C97.2, C98.2, C99.2, JP65.5, JP65.6, JP66.5, JP66.6, U65.2, U66.5, U66.10, U66.12
GND33: C100.2, C101.2, C102.2, JP67.5, JP67.6, JP68.5, JP68.6, U67.2, U68.5, U68.10, U68.12
GND34: C103.2, C104.2, C105.2, JP69.5, JP69.6, JP70.5, JP70.6, U69.2, U70.5, U70.10, U70.12
GND35: C106.2, C107.2, C108.2, JP71.5, JP71.6, JP72.5, JP72.6, U71.2, U72.5, U72.10, U72.12
GND36: C109.2, C110.2, C111.2, JP73.5, JP73.6, JP74.5, JP74.6, U73.2, U74.5, U74.10, U74.12
GND37: C112.2, C113.2, C114.2, JP75.5, JP75.6, JP76.5, JP76.6, U75.2, U76.5, U76.10, U76.12
GND38: C115.2, C116.2, C117.2, JP77.5, JP77.6, JP78.5, JP78.6, U77.2, U78.5, U78.10, U78.12
GND39: C118.2, C119.2, C120.2, JP79.5, JP79.6, JP80.5, JP80.6, U79.2, U80.5, U80.10, U80.12
GND40: C121.2, C122.2, C123.2, JP81.5, JP81.6, JP82.5, JP82.6, U81.2, U82.5, U82.10, U82.12
GND41: C124.2, C125.2, C126.2, JP83.5, JP83.6, JP84.5, JP84.6, U83.2, U84.5, U84.10, U84.12
GND42: C127.2, C128.2, C129.2, JP85.5, JP85.6, JP86.5, JP86.6, U85.2, U86.5, U86.10, U86.12
GND43: C130.2, C131.2, C132.2, JP87.5, JP87.6, JP88.5, JP88.6, U87.2, U88.5, U88.10, U88.12
GND44: C133.2, C134.2, C135.2, JP89.5, JP89.6, JP90.5, JP90.6, U89.2, U90.5, U90.10, U90.12
GND45: C136.2, C137.2, C138.2, JP91.5, JP91.6, JP92.5, JP92.6, U91.2, U92.5, U92.10, U92.12
GND46: C139.2, C140.2, C141.2, JP93.5, JP93.6, JP94.5, JP94.6, U93.2, U94.5, U94.10, U94.12
GND47: C142.2, C143.2, C144.2, JP95.5, JP95.6, JP96.5, JP96.6, U95.2, U96.5, U96.10, U96.12
GND48: C145.2, C146.2, C147.2, JP97.5, JP97.6, JP98.5, JP98.6, U97.2, U98.5, U98.10, U98.12
GND49: C148.2, C149.2, C150.2, JP99.5, JP99.6, JP100.5, JP100.6, U99.2, U100.5, U100.10, U100.12
GND50: C151.2, C152.2, C153.2, JP101.5, JP101.6, JP102.5, JP102.6, U101.2, U102.5, U102.10, U102.12
GND51: C154.2, C155.2, C156.2, JP103.5, JP103.6, JP104.5, JP104.6, U103.2, U104.5, U104.10, U104.12
GND52: C157.2, C158.2, C159.2, JP105.5, JP105.6, JP106.5, JP106.6, U105.2, U106.5, U106.10, U106.12
GND53: C160.2, C161.2, C162.2, JP107.5, JP107.6, JP108.5, JP108.6, U107.2, U108.5, U108.10, U108.12
GND54: C163.2, C164.2, C165.2, JP109.5, JP109.6, JP110.5, JP110.6, U109.2, U110.5, U110.10, U110.12
GND55: C166.2, C167.2, C168.2, JP111.5, JP111.6, JP112.5, JP112.6, U111.2, U112.5, U112.10, U112.12
GND56: C169.2, C170.2, C171.2, JP113.5, JP113.6, JP114.5, JP114.6, U113.2, U114.5, U114.10, U114.12
GND57: C172.2, C173.2, C174.2, JP115.5, JP115.6, JP116.5, JP116.6, U115.2, U116.5, U116.10, U116.12
GND58: C175.2, C176.2, C177.2, JP117.5, JP117.6, JP118.5, JP118.6, U117.2, U118.5, U118.10, U118.12
GND59: C178.2, C179.2, C180.2, JP119.5, JP119.6, JP120.5, JP120.6, U119.2, U120.5, U120.10, U120.12
GND60: C181.2, C182.2, C183.2, JP121.5, JP121.6, JP122.5, JP122.6, U121.2, U122.5, U122.10, U122.12
GND61: C184.2, C185.2, C186.2, JP123.5, JP123.6, JP124.5, JP124.6, U123.2, U124.5, U124.10, U124.12
GND62: C187.2, C188.2, C189.2, JP125.5, JP125.6, JP126.5, JP126.6, U125.2, U126.5, U126.10, U126.12
LSCL: Q2.2, R9.1, U1.4
LSCL1: Q4.2, R5.1, U4.4
LSCL2: Q6.2, R14.1, U6.4
LSCL3: Q8.2, R19.1, U8.4
LSCL4: Q10.2, R24.1, U10.4
LSCL5: Q12.2, R29.1, U12.4
LSCL6: Q14.2, R34.1, U14.4
LSCL7: Q16.2, R39.1, U16.4
LSCL8: Q18.2, R44.1, U18.4
LSCL9: Q20.2, R49.1, U20.4
LSCL10: Q22.2, R54.1, U22.4
LSCL11: Q24.2, R59.1, U24.4
LSCL12: Q26.2, R64.1, U26.4
LSCL13: Q28.2, R69.1, U28.4
LSCL14: Q30.2, R74.1, U30.4
LSCL15: Q32.2, R79.1, U32.4
LSCL16: Q34.2, R84.1, U34.4
LSCL17: Q36.2, R89.1, U36.4
LSCL18: Q38.2, R94.1, U38.4
LSCL19: Q40.2, R99.1, U40.4
LSCL20: Q42.2, R104.1, U42.4
LSCL21: Q44.2, R109.1, U44.4
LSCL22: Q46.2, R114.1, U46.4
LSCL23: Q48.2, R119.1, U48.4
LSCL24: Q50.2, R124.1, U50.4
LSCL25: Q52.2, R129.1, U52.4
LSCL26: Q54.2, R134.1, U54.4
LSCL27: Q56.2, R139.1, U56.4
LSCL28: Q58.2, R144.1, U58.4
LSCL29: Q60.2, R149.1, U60.4
LSCL30: Q62.2, R154.1, U62.4
LSCL31: Q64.2, R159.1, U64.4
LSCL32: Q66.2, R164.1, U66.4
LSCL33: Q68.2, R169.1, U68.4
LSCL34: Q70.2, R174.1, U70.4
LSCL35: Q72.2, R179.1, U72.4
LSCL36: Q74.2, R184.1, U74.4
LSCL37: Q76.2, R189.1, U76.4
LSCL38: Q78.2, R194.1, U78.4
LSCL39: Q80.2, R199.1, U80.4
LSCL40: Q82.2, R204.1, U82.4
LSCL41: Q84.2, R209.1, U84.4
LSCL42: Q86.2, R214.1, U86.4
LSCL43: Q88.2, R219.1, U88.4
LSCL44: Q90.2, R224.1, U90.4
LSCL45: Q92.2, R229.1, U92.4
LSCL46: Q94.2, R234.1, U94.4
LSCL47: Q96.2, R239.1, U96.4
LSCL48: Q98.2, R244.1, U98.4
LSCL49: Q100.2, R249.1, U100.4
LSCL50: Q102.2, R254.1, U102.4
LSCL51: Q104.2, R259.1, U104.4
LSCL52: Q106.2, R264.1, U106.4
LSCL53: Q108.2, R269.1, U108.4
LSCL54: Q110.2, R274.1, U110.4
LSCL55: Q112.2, R279.1, U112.4
LSCL56: Q114.2, R284.1, U114.4
LSCL57: Q116.2, R289.1, U116.4
LSCL58: Q118.2, R294.1, U118.4
LSCL59: Q120.2, R299.1, U120.4
LSCL60: Q122.2, R304.1, U122.4
LSCL61: Q124.2, R309.1, U124.4
LSCL62: Q126.2, R314.1, U126.4
LSDA: Q1.2, R8.1, U1.6
LSDA1: Q3.2, R4.1, U4.6
LSDA2: Q5.2, R13.1, U6.6
LSDA3: Q7.2, R18.1, U8.6
LSDA4: Q9.2, R23.1, U10.6
LSDA5: Q11.2, R28.1, U12.6
LSDA6: Q13.2, R33.1, U14.6
LSDA7: Q15.2, R38.1, U16.6
LSDA8: Q17.2, R43.1, U18.6
LSDA9: Q19.2, R48.1, U20.6
LSDA10: Q21.2, R53.1, U22.6
LSDA11: Q23.2, R58.1, U24.6
LSDA12: Q25.2, R63.1, U26.6
LSDA13: Q27.2, R68.1, U28.6
LSDA14: Q29.2, R73.1, U30.6
LSDA15: Q31.2, R78.1, U32.6
LSDA16: Q33.2, R83.1, U34.6
LSDA17: Q35.2, R88.1, U36.6
LSDA18: Q37.2, R93.1, U38.6
LSDA19: Q39.2, R98.1, U40.6
LSDA20: Q41.2, R103.1, U42.6
LSDA21: Q43.2, R108.1, U44.6
LSDA22: Q45.2, R113.1, U46.6
LSDA23: Q47.2, R118.1, U48.6
LSDA24: Q49.2, R123.1, U50.6
LSDA25: Q51.2, R128.1, U52.6
LSDA26: Q53.2, R133.1, U54.6
LSDA27: Q55.2, R138.1, U56.6
LSDA28: Q57.2, R143.1, U58.6
LSDA29: Q59.2, R148.1, U60.6
LSDA30: Q61.2, R153.1, U62.6
LSDA31: Q63.2, R158.1, U64.6
LSDA32: Q65.2, R163.1, U66.6
LSDA33: Q67.2, R168.1, U68.6
LSDA34: Q69.2, R173.1, U70.6
LSDA35: Q71.2, R178.1, U72.6
LSDA36: Q73.2, R183.1, U74.6
LSDA37: Q75.2, R188.1, U76.6
LSDA38: Q77.2, R193.1, U78.6
LSDA39: Q79.2, R198.1, U80.6
LSDA40: Q81.2, R203.1, U82.6
LSDA41: Q83.2, R208.1, U84.6
LSDA42: Q85.2, R213.1, U86.6
LSDA43: Q87.2, R218.1, U88.6
LSDA44: Q89.2, R223.1, U90.6
LSDA45: Q91.2, R228.1, U92.6
LSDA46: Q93.2, R233.1, U94.6
LSDA47: Q95.2, R238.1, U96.6
LSDA48: Q97.2, R243.1, U98.6
LSDA49: Q99.2, R248.1, U100.6
LSDA50: Q101.2, R253.1, U102.6
LSDA51: Q103.2, R258.1, U104.6
LSDA52: Q105.2, R263.1, U106.6
LSDA53: Q107.2, R268.1, U108.6
LSDA54: Q109.2, R273.1, U110.6
LSDA55: Q111.2, R278.1, U112.6
LSDA56: Q113.2, R283.1, U114.6
LSDA57: Q115.2, R288.1, U116.6
LSDA58: Q117.2, R293.1, U118.6
LSDA59: Q119.2, R298.1, U120.6
LSDA60: Q121.2, R303.1, U122.6
LSDA61: Q123.2, R308.1, U124.6
LSDA62: Q125.2, R313.1, U126.6
unnamed: C3.1, U1.2
unnamed: C6.1, U4.2
unnamed: I2C.3, R7.2
unnamed: I2C.1, R10.2
unnamed: I2C1.3, R3.2
unnamed: I2C1.1, R6.2
unnamed: C9.1, U6.2
unnamed: I2C2.3, R12.2
unnamed: I2C2.1, R15.2
unnamed: C12.1, U8.2
unnamed: I2C3.3, R17.2
unnamed: I2C3.1, R20.2
unnamed: C15.1, U10.2
unnamed: I2C4.3, R22.2
unnamed: I2C4.1, R25.2
unnamed: C18.1, U12.2
unnamed: I2C5.3, R27.2
unnamed: I2C5.1, R30.2
unnamed: C21.1, U14.2
unnamed: I2C6.3, R32.2
unnamed: I2C6.1, R35.2
unnamed: C24.1, U16.2
unnamed: I2C7.3, R37.2
unnamed: I2C7.1, R40.2
unnamed: C27.1, U18.2
unnamed: I2C8.3, R42.2
unnamed: I2C8.1, R45.2
unnamed: C30.1, U20.2
unnamed: I2C9.3, R47.2
unnamed: I2C9.1, R50.2
unnamed: C33.1, U22.2
unnamed: I2C10.3, R52.2
unnamed: I2C10.1, R55.2
unnamed: C36.1, U24.2
unnamed: I2C11.3, R57.2
unnamed: I2C11.1, R60.2
unnamed: C39.1, U26.2
unnamed: I2C12.3, R62.2
unnamed: I2C12.1, R65.2
unnamed: C42.1, U28.2
unnamed: I2C13.3, R67.2
unnamed: I2C13.1, R70.2
unnamed: C45.1, U30.2
unnamed: I2C14.3, R72.2
unnamed: I2C14.1, R75.2
unnamed: C48.1, U32.2
unnamed: I2C15.3, R77.2
unnamed: I2C15.1, R80.2
unnamed: C51.1, U34.2
unnamed: I2C16.3, R82.2
unnamed: I2C16.1, R85.2
unnamed: C54.1, U36.2
unnamed: I2C17.3, R87.2
unnamed: I2C17.1, R90.2
unnamed: C57.1, U38.2
unnamed: I2C18.3, R92.2
unnamed: I2C18.1, R95.2
unnamed: C60.1, U40.2
unnamed: I2C19.3, R97.2
unnamed: I2C19.1, R100.2
unnamed: C63.1, U42.2
unnamed: I2C20.3, R102.2
unnamed: I2C20.1, R105.2
unnamed: C66.1, U44.2
unnamed: I2C21.3, R107.2
unnamed: I2C21.1, R110.2
unnamed: C69.1, U46.2
unnamed: I2C22.3, R112.2
unnamed: I2C22.1, R115.2
unnamed: C72.1, U48.2
unnamed: I2C23.3, R117.2
unnamed: I2C23.1, R120.2
unnamed: C75.1, U50.2
unnamed: I2C24.3, R122.2
unnamed: I2C24.1, R125.2
unnamed: C78.1, U52.2
unnamed: I2C25.3, R127.2
unnamed: I2C25.1, R130.2
unnamed: C81.1, U54.2
unnamed: I2C26.3, R132.2
unnamed: I2C26.1, R135.2
unnamed: C84.1, U56.2
unnamed: I2C27.3, R137.2
unnamed: I2C27.1, R140.2
unnamed: C87.1, U58.2
unnamed: I2C28.3, R142.2
unnamed: I2C28.1, R145.2
unnamed: C90.1, U60.2
unnamed: I2C29.3, R147.2
unnamed: I2C29.1, R150.2
unnamed: C93.1, U62.2
unnamed: I2C30.3, R152.2
unnamed: I2C30.1, R155.2
unnamed: C96.1, U64.2
unnamed: I2C31.3, R157.2
unnamed: I2C31.1, R160.2
unnamed: C99.1, U66.2
unnamed: I2C32.3, R162.2
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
